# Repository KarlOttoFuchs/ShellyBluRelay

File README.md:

# ESP32C3 Relay Module

A BLE-enabled relay controller for home automation. Connect Shelly BLU sensors to switch 12-24V loads — no WiFi, no cloud, no app required.

> **Note:** This project is provided as-is. No support, issues, or pull requests will be addressed.

This repository also holds the **LED Strip Controller** (`FEHA-LSC-001`, in design): a 24 V COB
LED-strip dimmer in an inline printed tube. See [`Hardware/README.md`](Hardware/README.md) and
the design spec [`Docs/design/led-strip-controller-design.md`](Docs/design/led-strip-controller-design.md).
The rest of this README describes the relay module (`FEHA-RM-001` Rev A).

## Features

- **BTHome v2 sensor support** — Shelly BLU Button, Motion, and Door/Window sensors
- **30-second learning mode** — just press a button and trigger your sensor
- **Button-based timer presets** — 30s, 60s, 120s, or 300s (no computer needed)
- **Optional serial interface** — for advanced configuration and debugging
- **Safety-first design** — watchdog timer, fail-safe relay defaults (OFF on boot/reset)

## Default Settings

| Setting | Default | Description |
|---------|---------|-------------|
| Timer | 300 seconds | How long relay stays on after trigger |
| Retrigger | EXTEND | New triggers reset the timer countdown |
| State | UNCONFIGURED | Waiting for sensor registration |

## Quick Start (Button Only — No Serial Needed!)

1. **Power on** the module via USB-C or DC input → Status LED is OFF (unconfigured)
2. **Long press** the button for 2+ seconds → Status LED fast blinks (learning mode)
3. **Trigger your sensor** within 30 seconds (press button, wave at motion sensor, open door)
4. **Sensor registered** → Status LED slow blinks (listening, ready to use)
5. **Done!** Your sensor now controls the relay with a 5-minute timer

### Changing the Timer (Button Only)

While in listening mode (slow blink), use short presses to cycle through timer presets:

1. **Short press** (< 0.5 sec) → LED shows current preset with counted blinks
2. **Short press again** → Cycles to next preset
3. **Wait 5 seconds** → Preset saved automatically

| LED Blinks | Timer Duration |
|------------|----------------|
| 1 blink | 30 seconds |
| 2 blinks | 60 seconds |
| 3 blinks | 120 seconds |
| 4 blinks | 300 seconds (default) |

Settings persist across power cycles.

## LED Status Patterns

### Status LED (White)

| Pattern | Meaning |
|---------|---------|
| OFF | Unconfigured — no sensor registered |
| Fast blink (250ms) | Learning mode — 30 second window active |
| Slow blink (1s) | Listening — ready for sensor triggers |
| Solid ON | Relay active — timer running |

### Error LED (Red)

| Pattern | Meaning |
|---------|---------|
| 1 blink | Sensor battery low (< 20%) |
| 2 blinks | NVS storage error |
| 3 blinks | BLE initialization failure |

## Example: Motion-Activated Under-Counter Lights

Use a Shelly BLU Motion sensor to automatically turn on kitchen LED strip lighting.

**Wiring:**
- Connect 12V LED strip positive to relay **NO** (Normally Open) terminal
- Connect LED strip negative to power supply ground
- Connect relay **COM** (Common) to 12V power supply positive
- Power the module via the same 12V supply (DC input) or separate USB-C

**Setup:**
1. Power on the module
2. Long press button (2+ seconds) → fast blink
3. Walk past the motion sensor → sensor registered, slow blink
4. Short press button twice → cycles to 60-second preset (2 blinks)
5. Wait 5 seconds → preset saved

**Result:** Motion now triggers 60 seconds of under-counter lighting!

## Hardware Overview

- **MCU**: ESP32-C3-MINI-1 (RISC-V, BLE 5.0)
- **Relay**: 10A contacts (NO/NC/COM), 3VDC coil
- **Power**: USB-C (5V) or external DC (12-24V) with auto-switching
- **Interface**: Physical button + status/error LEDs

### GPIO Pinout

| GPIO | Function |
|------|----------|
| 0 | Error LED (red) |
| 7 | Relay control |
| 9 | User button (active low) |
| 10 | Status LED (white) |

## Serial Interface (Advanced)

Connect via USB at **115200 baud** for advanced configuration:

| Command | Description |
|---------|-------------|
| `STATUS` | Show current state, sensor info, timer settings |
| `RELAY ON` / `RELAY OFF` | Manual relay control for testing |
| `SET_TIMER <1-600>` | Set timer duration in seconds |
| `SET_RETRIGGER EXTEND` | New triggers reset timer (default) |
| `SET_RETRIGGER IGNORE` | Ignore triggers while relay active |
| `BLE_EVENTS` | Show last 10 sensor trigger events |
| `CLEAR_SENSOR` | Unregister sensor, return to unconfigured |
| `HELP` | List all commands |

## Building the Firmware

### Prerequisites

- ESP-IDF v5.1.x or v5.2.x LTS
- ESP32-C3 target configured

### Build & Flash

```bash
cd Firmware/esp32c3-relay-firmware

# First time only
idf.py set-target esp32c3

# Build and flash
idf.py build flash -p /dev/ttyUSB0

# Monitor serial output
idf.py monitor -p /dev/ttyUSB0
```

## Documentation

- [Architecture & Serial Protocol](Firmware/esp32c3-relay-firmware/docs/architecture.md)
- [Hardware Pin Mapping](Hardware/ESP32C3-Relay-Module-Rev-A/ESP32C3-Pin-Mapping.md)
- [Firmware README](Firmware/esp32c3-relay-firmware/README.md)

## License

MIT License — see [LICENSE](LICENSE) for details.

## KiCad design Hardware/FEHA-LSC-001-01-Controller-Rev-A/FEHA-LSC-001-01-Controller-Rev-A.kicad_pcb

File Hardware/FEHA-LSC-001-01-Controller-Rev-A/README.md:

# FEHA-LSC-001-01 Rev A — LED Strip Controller

24 V COB LED-strip controller, Shelly BLU / BLE triggered, ESP32-C3

**Status:** Manufacturing files generated 2026-10-07 — schematic and layout gates closed
2026-10-06 (50 × 30 mm, 4 layers, routed). Next: fab gate review (fiducials, position file). See [`DESIGN-CHANGES.md`](DESIGN-CHANGES.md) for the
change record and the design spec in
[`../../Docs/design/led-strip-controller-design.md`](../../Docs/design/led-strip-controller-design.md)
for intent, architecture and mechanical constraints — this README does not restate them.

## Project layout

- `FEHA-LSC-001-01-Controller-Rev-A.kicad_pro` / `.kicad_sch` / `.kicad_pcb`
- `Library/_FEHA-LSC-001.kicad_sym` + `Library/_FEHA-LSC-001.pretty/` — the **project-local** symbol and
  footprint libraries, wired in via `sym-lib-table` / `fp-lib-table` using `${KIPRJMOD}`. The
  nickname comes from the product part number, not the directory name.
- `Library/3DModels/` — STEP models, referenced as `${KIPRJMOD}/Library/3DModels/<name>.step`.
- `Library/_FEHA-LSC-001.kicad_blocks/` — the project **design-block** library (`design-block-lib-table`)
  for reusable schematic/layout fragments; empty until a block is saved into it from KiCad.
- `scripts/lcsc_to_kicad.py` — imports LCSC/EasyEDA parts into the project library.
- `scripts/setup_board.py` — board setup: outline and antenna notch, centre origin, keep-out
  rule areas, GND pours (re-runnable; see its docstring).
- `production/` — fab outputs from the KiCad Fabrication Toolkit (2026-10-07):
  `LED_Strip_Controller_A.zip` (Gerbers and drill files), `bom.csv`, `positions.csv`,
  `designators.csv`, `netlist.ipc`. The toolkit names the zip from the board title and
  revision, not the `FEHA-LSC-001-01-Controller-Rev-A-<fab>-<YYYYMMDD>.zip` convention.

## Tooling

`kicad-cli` is not on PATH:
`/Applications/KiCad/KiCad.app/Contents/MacOS/kicad-cli`

Files are **KiCad 10 format** (`version 20260306`).

## Revision history

- Rev A — initial design: schematic and layout complete, manufacturing files generated
  2026-10-07, not yet ordered.

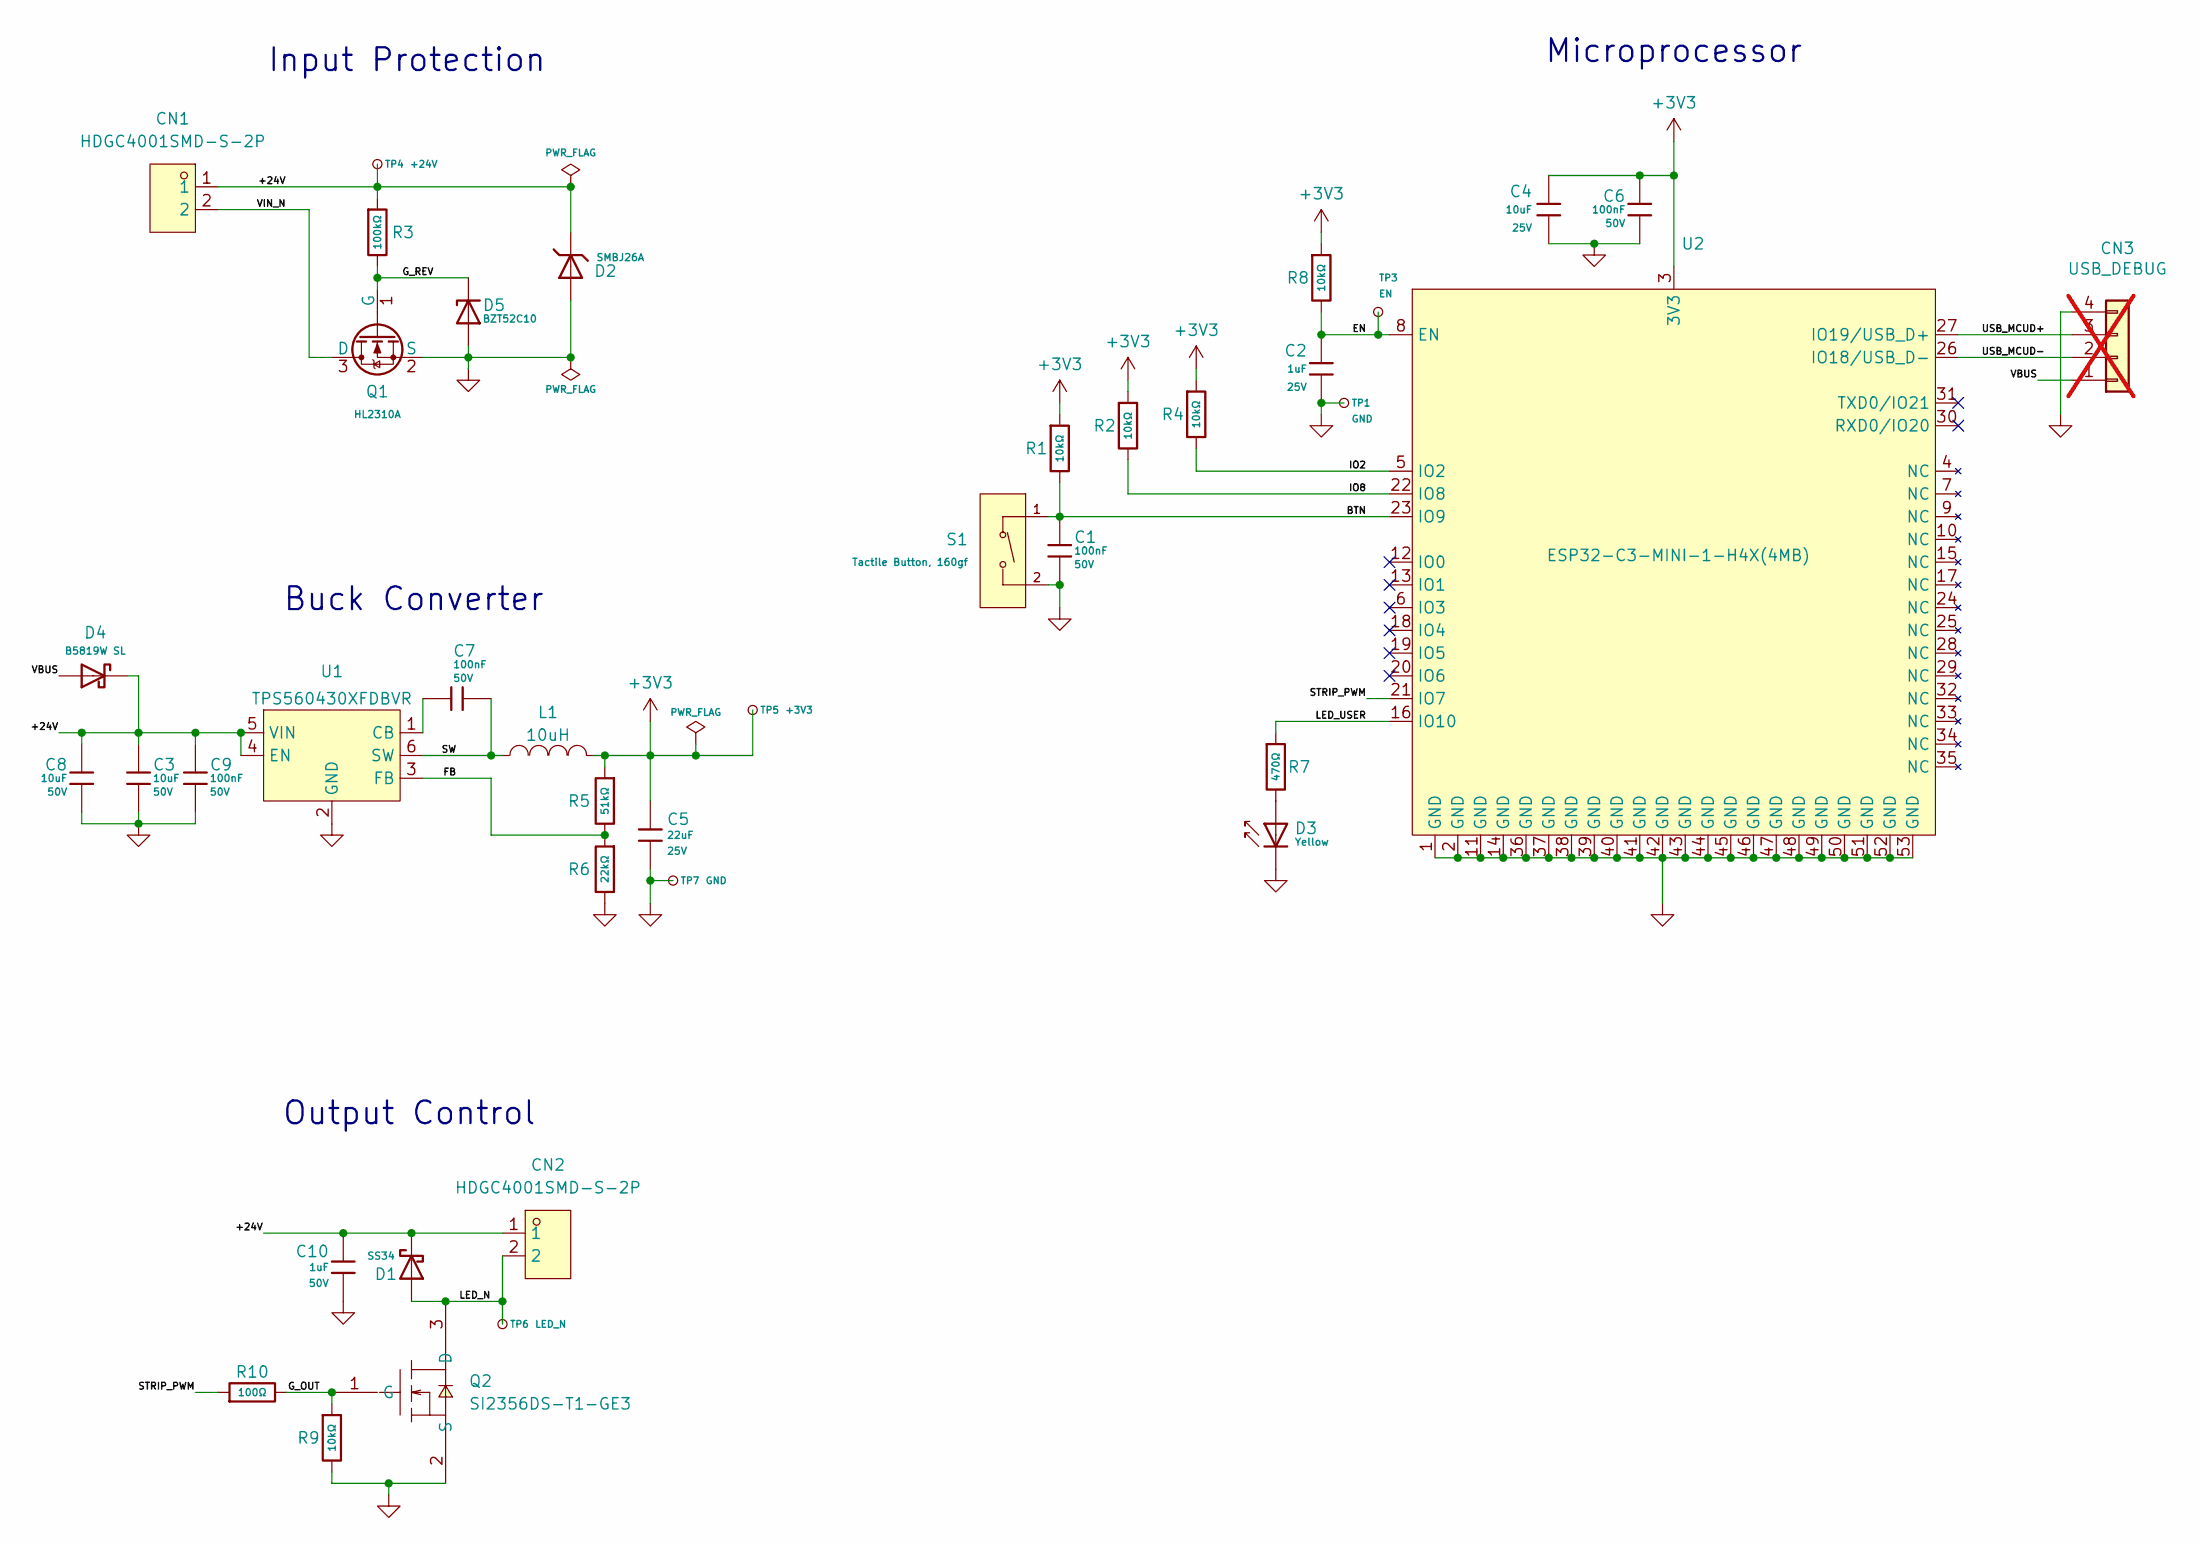
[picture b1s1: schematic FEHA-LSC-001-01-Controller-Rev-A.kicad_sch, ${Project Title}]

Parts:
C1, C6, C7, C9: 100nF; C_0402; Voltage Rated 50V; Tolerance ±10%; Part CL05B104KB54PNC; LCSC C307331
C2: 1uF; C_0402; Voltage Rated 25V; Tolerance ±10%; Part CL05A105KA5NQNC; LCSC C52923
C3, C8: 10uF; C_1206; Voltage Rated 50V; Tolerance ±10%; Part CL31A106KBHNNNE; LCSC C13585
C4: 10uF; C_0603; Voltage Rated 25V; Tolerance ±20%; Part CL10A106MA8NRNC; LCSC C96446
C5: 22uF; C_1206; Voltage Rated 25V; Tolerance ±10%; Part CL31A226KAHNNNE; LCSC C12891
C10: 1uF; C_0805; Voltage Rated 50V; Tolerance ±10%; Part CL21B105KBFNNNE; LCSC C28323
CN1, CN2: HDGC4001SMD-S-2P; CONN-SMD_2P-P4.00_HDGC4001SMD-S-2P; Mfr. Part # HDGC4001SMD-S-2P; LCSC Part # C5197184
CN3: USB_DEBUG; PinHeader_1x04_P2.54mm_Vertical_Lock; not fitted
D1: SS34; D_SMA; Forward Voltage (Vf@If) 550mV@3A; Reverse Voltage (Vr) 40V; Part SS34; LCSC C8678
D2: SMBJ26A; D_SMB; Part SMBJ26A; LCSC C19077580
D3: Yellow; D_0805; Part KT-0805Y; LCSC C2296
D4: B5819W SL; D_SOD-123; Forward Voltage (Vf@If) 600mV@1A; Reverse Voltage (Vr) 40V; Part B5819W SL; LCSC C8598
D5: BZT52C10; D_SOD-123; Part BZT52C10; LCSC C19077408
L1: 10uH; IND-SMD_L4.4-W4.2; Tolerance ±20%; Mfr. Part # FXL0420-100-M; LCSC Part # C177242
Q1: HL2310A; Q_SOT-23; Part HL2310A; LCSC C7420347
Q2: SI2356DS-T1-GE3; SOT-23_L2.9-W1.3-P1.90-LS2.4-BR; Mfr. Part # SI2356DS-T1-GE3; LCSC Part # C74127
R1, R2, R4, R8, R9: 10kΩ; R_0402; Overload Voltage (Max) 50V; Tolerance ±1%; Part 0402WGF1002TCE; LCSC C25744
R3: 100kΩ; R_0402; Overload Voltage (Max) 50V; Tolerance ±1%; Part 0402WGF1003TCE; LCSC C25741
R5: 51kΩ; R_0402; Overload Voltage (Max) 50V; Tolerance ±1%; Part 0402WGF5102TCE; LCSC C25794
R6: 22kΩ; R_0402; Overload Voltage (Max) 50V; Tolerance ±1%; Part 0402WGF2202TCE; LCSC C25768
R7: 470Ω; R_0402; Overload Voltage (Max) 50V; Tolerance ±1%; Part 0402WGF4700TCE; LCSC C25117
R10: 100Ω; R_0402; Overload Voltage (Max) 50V; Tolerance ±1%; Part 0402WGF1000TCE; LCSC C25076
S1: Tactile Button, 160gf; SW_TS-1088-AR02016; Voltage Rating (Dc) 12V; Part TS-1088-AR02016; LCSC C720477
TP1, TP7: GND; TestPoint_Pad_D1.5mm
TP3: EN; TestPoint_Pad_D1.5mm
TP4: +24V; TestPoint_Pad_D1.5mm
TP5: +3V3; TestPoint_Pad_D1.5mm
TP6: LED_N; TestPoint_Pad_D1.5mm
U1: TPS560430XFDBVR; SOT-23-6_L2.9-W1.6-P0.95-LS2.8-BR; Mfr. Part # TPS560430XFDBVR; LCSC Part # C523980
U2: ESP32-C3-MINI-1-H4X(4MB); WIFIM-SMD_ESP32-C3-MINI-1; Mfr. Part # ESP32-C3-MINI-1-H4X; LCSC Part # C41349510

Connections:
+3V3: C4.1, C5.1, C6.1, L1.1, R1.1, R2.1, R4.1, R5.1, R8.1, TP5.1 (1_1), U2.3 (3V3)
/+24V: C3.1, C8.1, C9.1, C10.1, CN1.1, CN2.1, D1.1, D2.1, D4.1, R3.1, TP4.1 (1_1), U1.4 (EN), U1.5 (VIN)
/BTN: C1.1, R1.2, S1.1 (A), U2.23 (IO9)
/EN: C2.1, R8.2, TP3.1 (1_1), U2.8 (EN)
/FB: R5.2, R6.1, U1.3 (FB)
/G_OUT: Q2.1 (G), R9.1, R10.2
/G_REV: D5.1, Q1.1 (G), R3.2
/IO2: R4.2, U2.5 (IO2)
/IO8: R2.2, U2.22 (IO8)
/LED_N: CN2.2, D1.2, Q2.3 (D), TP6.1 (1_1)
/LED_USER: R7.1, U2.16 (IO10)
/STRIP_PWM: R10.1, U2.21 (IO7)
/SW: C7.2, L1.2, U1.6 (SW)
/USB_MCUD+: CN3.3, U2.27 (IO19/USB_D+)
/USB_MCUD-: CN3.2, U2.26 (IO18/USB_D-)
/VBUS: CN3.1, D4.2
/VIN_N: CN1.2, Q1.3 (D)
GND: C1.2, C2.2, C3.2, C4.2, C5.2, C6.2, C8.2, C9.2, C10.2, CN3.4, D2.2, D3.1, D5.2, Q1.2 (S), Q2.2 (S), R6.2, R9.2, S1.2 (B), TP1.1 (1_1), TP7.1 (1_1), U1.2 (GND), U2.1 (GND), U2.2 (GND), U2.11 (GND), U2.14 (GND), U2.36 (GND), U2.37 (GND), U2.38 (GND), U2.39 (GND), U2.40 (GND), U2.41 (GND), U2.42 (GND), U2.43 (GND), U2.44 (GND), U2.45 (GND), U2.46 (GND), U2.47 (GND), U2.48 (GND), U2.49 (GND), U2.50 (GND), U2.51 (GND), U2.52 (GND), U2.53 (GND)
unnamed: D3.2, R7.2
unnamed: C7.1, U1.1 (CB)

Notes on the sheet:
Input Protection
Output Control
Microprocessor
Buck Converter

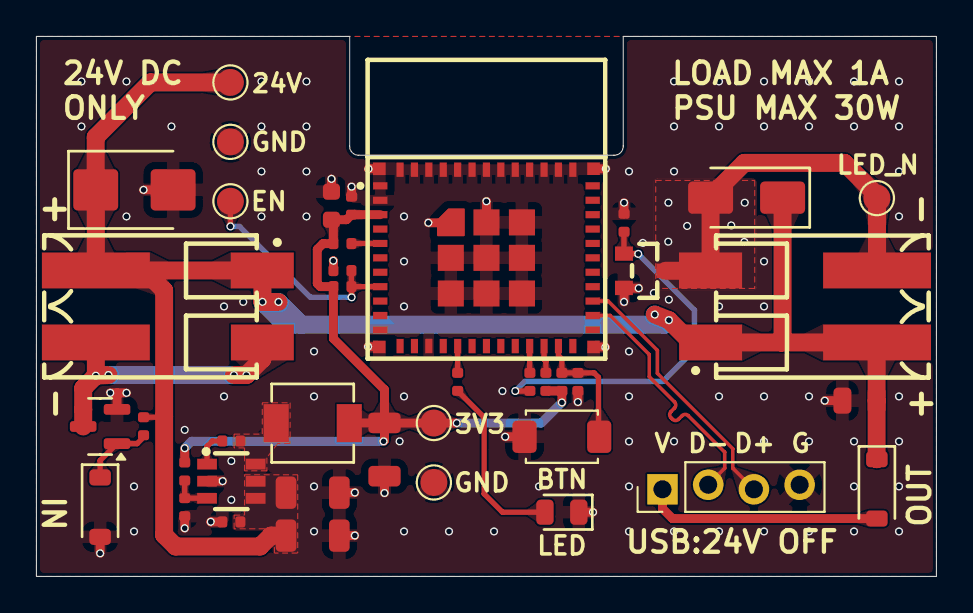
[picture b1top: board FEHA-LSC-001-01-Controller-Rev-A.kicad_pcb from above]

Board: 4 copper layers, 50.0 x 30.0 mm, 40 parts (0 on the bottom side), 20 nets.

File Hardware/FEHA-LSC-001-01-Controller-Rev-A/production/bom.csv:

Designator,Footprint,Quantity,Value,LCSC Part #
"C1, C6, C7, C9",C_0402,4,100nF,C307331
C10,C_0805,1,1uF,C28323
C2,C_0402,1,1uF,C52923
"C3, C8",C_1206,2,10uF,C13585
C4,C_0603,1,10uF,C96446
C5,C_1206,1,22uF,C12891
"CN1, CN2",CONN-SMD_2P-P4.00_HDGC4001SMD-S-2P,2,HDGC4001SMD-S-2P,C5197184
D1,D_SMA,1,SS34,C8678
D2,D_SMB,1,SMBJ26A,C19077580
D3,D_0805,1,Yellow,C2296
D4,D_SOD-123,1,B5819W SL,C8598
D5,D_SOD-123,1,BZT52C10,C19077408
L1,IND-SMD_L4.4-W4.2,1,10uH,C177242
Q1,Q_SOT-23,1,HL2310A,C7420347
Q2,SOT-23_L2.9-W1.3-P1.90-LS2.4-BR,1,SI2356DS-T1-GE3,C74127
"R1, R2, R4, R8, R9",R_0402,5,10kΩ,C25744
R10,R_0402,1,100Ω,C25076
R3,R_0402,1,100kΩ,C25741
R5,R_0402,1,51kΩ,C25794
R6,R_0402,1,22kΩ,C25768
R7,R_0402,1,470Ω,C25117
S1,SW_TS-1088-AR02016,1,"Tactile Button, 160gf",C720477
U1,SOT-23-6_L2.9-W1.6-P0.95-LS2.8-BR,1,TPS560430XFDBVR,C523980
U2,WIFIM-SMD_ESP32-C3-MINI-1,1,ESP32-C3-MINI-1-H4X(4MB),C41349510

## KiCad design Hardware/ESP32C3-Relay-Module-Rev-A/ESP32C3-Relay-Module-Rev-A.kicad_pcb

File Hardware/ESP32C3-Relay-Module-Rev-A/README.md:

# FEHA-RM-001 Rev A — ESP32-C3 Relay Module

BLE-triggered relay module: ESP32-C3-MINI-1-H4, SRD-03VDC-SL-C relay (3 V coil, AO3400A driver),
AP63203 3.3 V buck, USB-C or 5–24 V DC input, push button and status LEDs.

**Status:** Fabricated (JLCPCB). The KiCad files are frozen and must match the boards in hand.

## Project layout

- `ESP32C3-Relay-Module-Rev-A.kicad_pro` / `.kicad_sch` / `.kicad_pcb` — the design. The
  directory and file stem predate the `<PN>-<Slug>-Rev-<X>` convention and are kept as built.
- `ESP32C3-Pin-Mapping.md` — GPIO and connector map for this board.
- `production/` — the fabrication outputs that were ordered (`ESP32C3_Relay_Module_A.zip`, BOM,
  placement, IPC netlist).

## Libraries

This revision has **no project-local library**. Symbols and footprints resolve from machine-global
libraries: the custom library (`${CUSTOM_LIBRARY}`), the JLCPCB plugin library and KiCad's
3rd-party folder (`${KICAD8_3RD_PARTY}`). On a machine without them the schematic and board open
with missing parts.

## Revision history

- Rev A — first build.

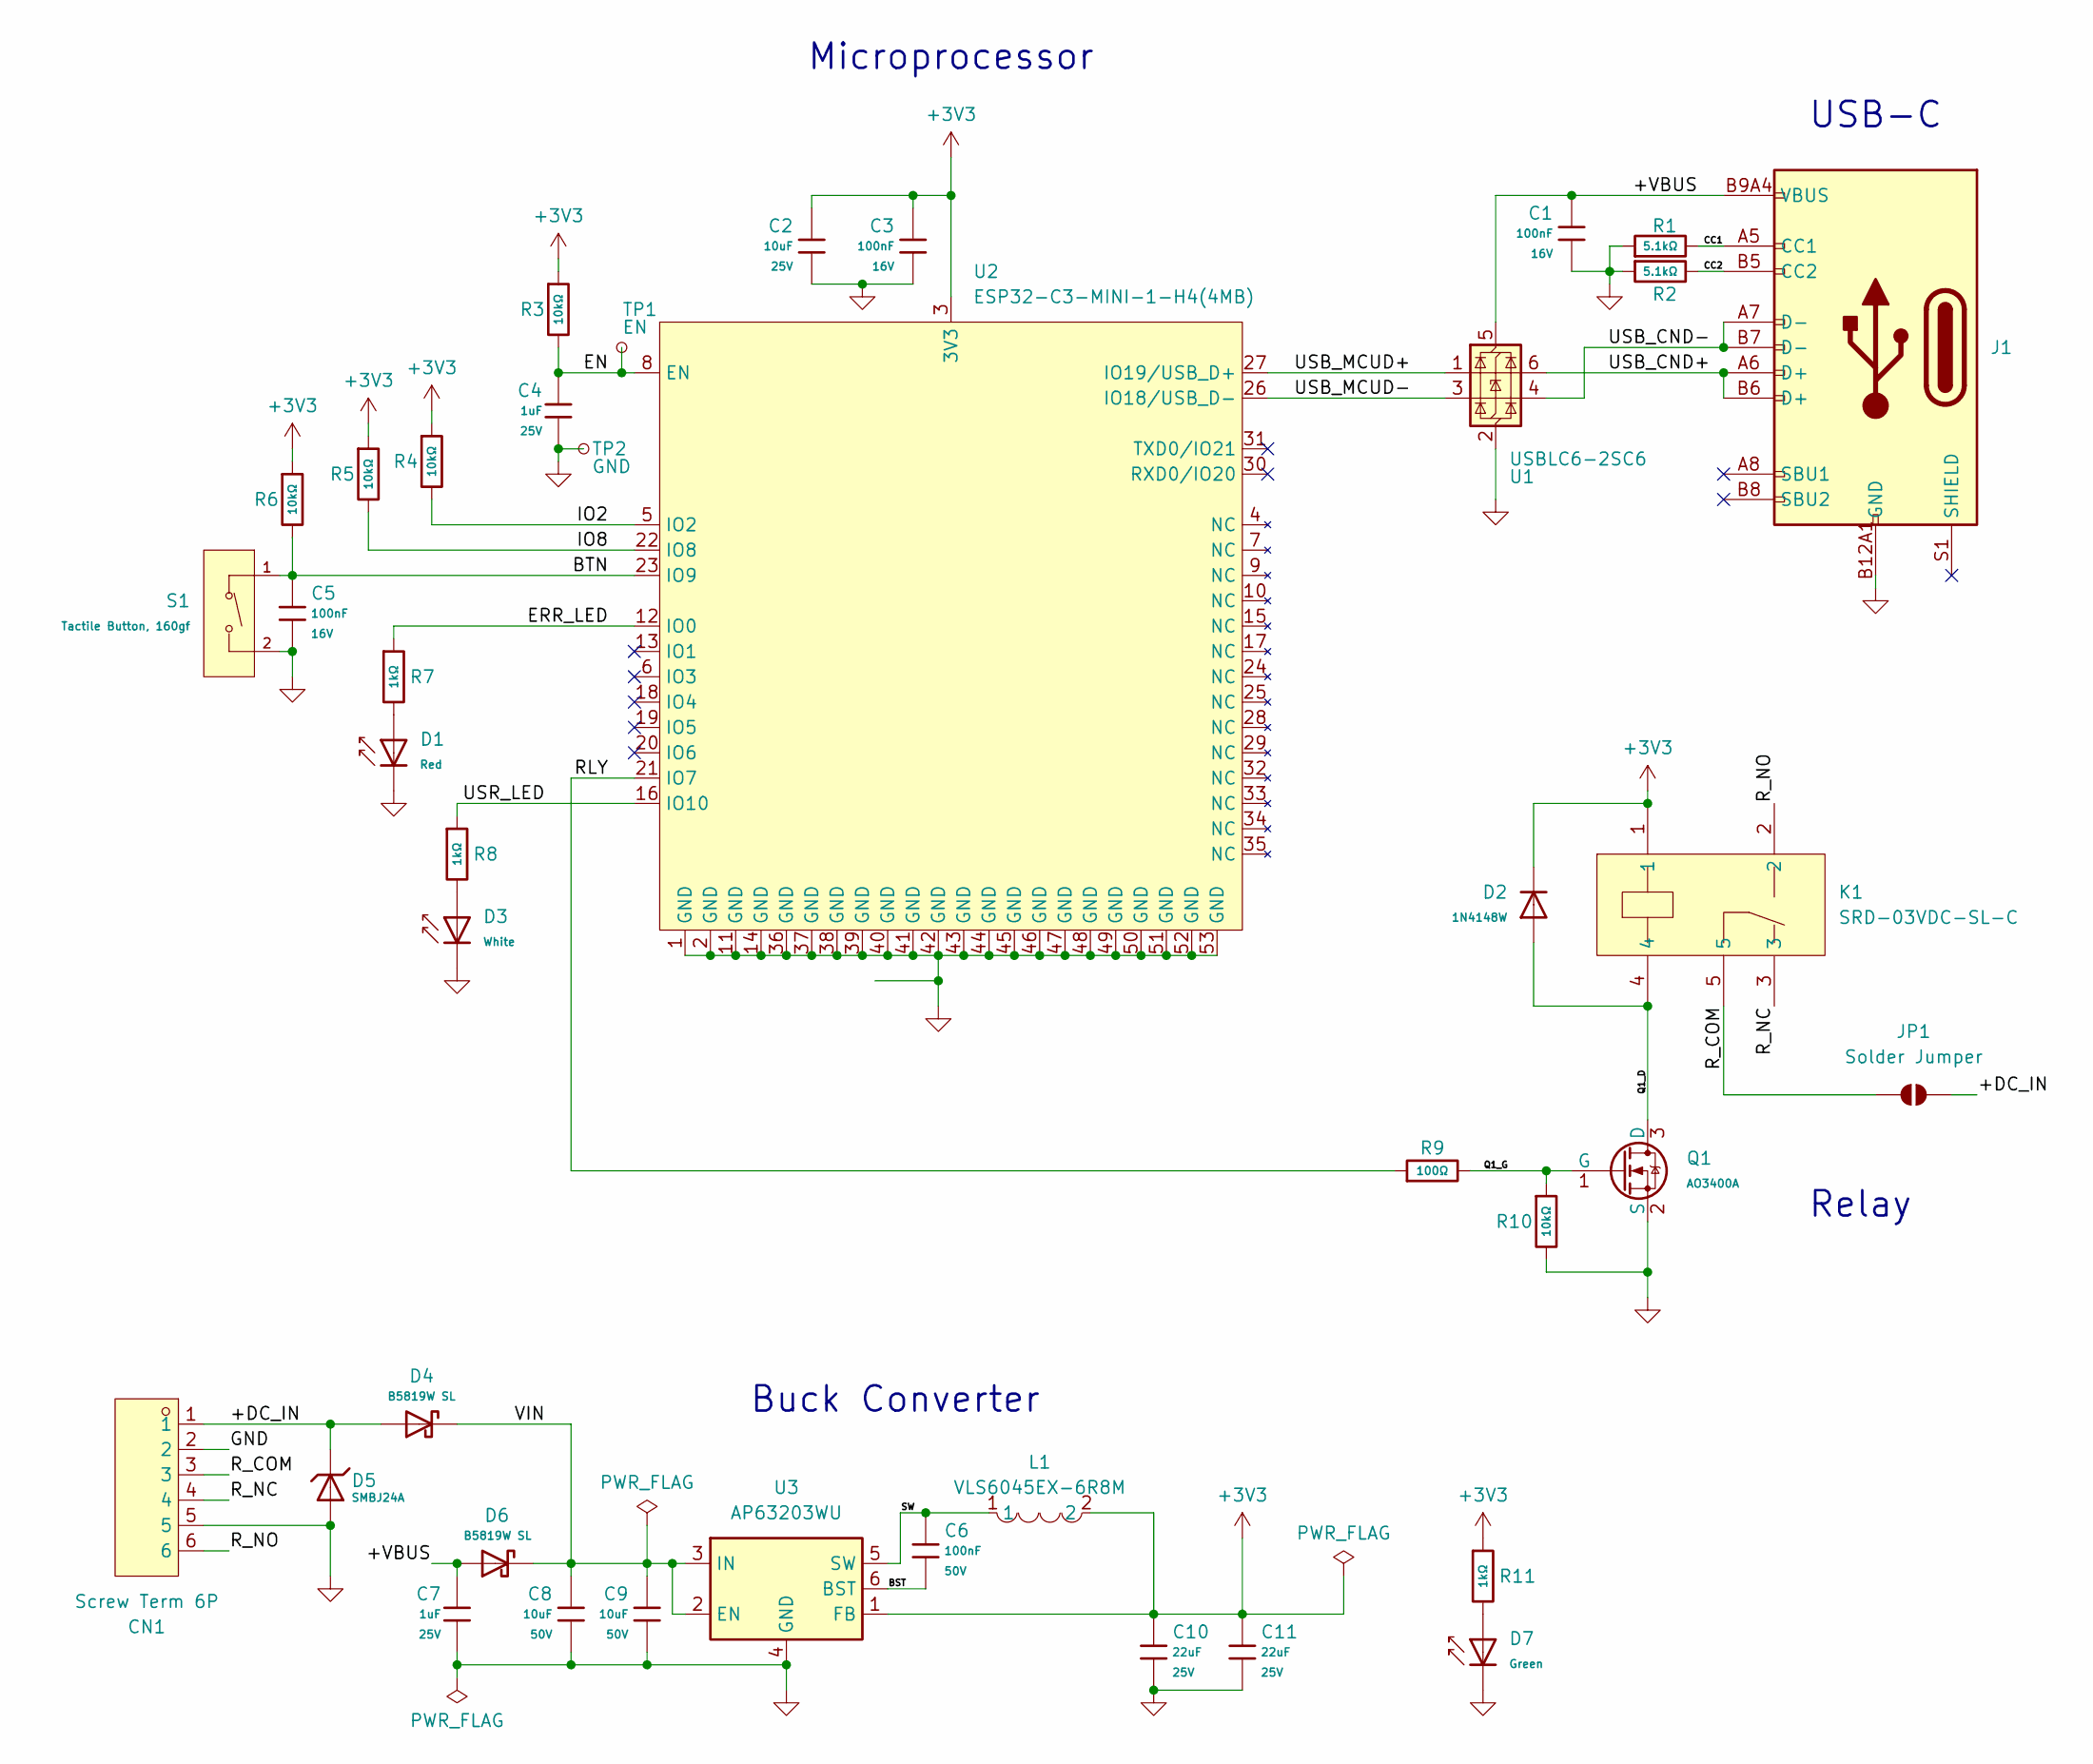
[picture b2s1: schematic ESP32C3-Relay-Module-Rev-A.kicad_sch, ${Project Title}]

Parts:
C1, C3, C5: 100nF; C_0402; Voltage Rated 16V; Tolerance ±10%; Part CL05B104KO5NNNC; LCSC C1525
C2: 10uF; C_0603; Voltage Rated 25V; Tolerance ±20%; Part CL10A106MA8NRNC; LCSC C96446
C4, C7: 1uF; C_0402; Voltage Rated 25V; Tolerance ±10%; Part CL05A105KA5NQNC; LCSC C52923
C6: 100nF; C_0603; Voltage Rated 50V; Tolerance ±10%; Part CC0603KRX7R9BB104; LCSC C14663
C8, C9: 10uF; C_1206; Voltage Rated 50V; Tolerance ±10%; Part CL31A106KBHNNNE; LCSC C13585
C10, C11: 22uF; C_1206; Voltage Rated 25V; Tolerance ±10%; Part CL31A226KAHNNNE; LCSC C12891
CN1: Screw Term 6P; CONN-TH_6P-MX128-5.08-GN01-06P-CU-Y-A; Mfr. Part # MX128-5.08-06P-GN01-Cu-Y-A; LCSC Part C5290379
D1: Red; D_0805; Forward Voltage (VF) 1.6V~2.6V; Part NCD0805R1; LCSC C84256
D2: 1N4148W; D_SOD-123; Forward Voltage (Vf@If) 1.25V@150mA; Reverse Voltage (Vr) 100V; Part 1N4148W; LCSC C7420318
D3: White; D_0805; Part KT-0805W; LCSC C34499
D4, D6: B5819W SL; D_SOD-123; Forward Voltage (Vf@If) 600mV@1A; Reverse Voltage (Vr) 40V; Part B5819W SL; LCSC C8598
D5: SMBJ24A; D_SMB; Part SMBJ24A; LCSC C19077578
D7: Green; D_0805; Part KT-0805G; LCSC C2297
J1: Connector, USB-TYPE-C-16P; TYPE-C-SMD_HX-TYPE-C-16PIN; Mfr. Part # USB-TYPE-C-019; LCSC C2927039
JP1: Solder Jumper; SolderJumper-2_P1.3mm_Open_RoundedPad1.0x1.5mm
K1: SRD-03VDC-SL-C; RELAY-TH_SRD-XXVDC-XL-C; Mfr. Part # SRD-03VDC-SL-C; LCSC Part # C24585
L1: VLS6045EX-6R8M; IND-SMD_L6.0-W6.0; Mfr. Part # VLS6045EX-6R8M; LCSC Part # C415364
Q1: AO3400A; Q_SOT-23; Part AO3400A; LCSC C20917
R1, R2: 5.1kΩ; R_0402; Overload Voltage (Max) 50V; Tolerance ±1%; Part 0402WGF5101TCE; LCSC C25905
R3, R4, R5, R6, R10: 10kΩ; R_0402; Overload Voltage (Max) 50V; Tolerance ±1%; Part 0402WGF1002TCE; LCSC C25744
R7, R8, R11: 1kΩ; R_0402; Overload Voltage (Max) 50V; Tolerance ±1%; Part 0402WGF1001TCE; LCSC C11702
R9: 100Ω; R_0402; Overload Voltage (Max) 50V; Tolerance ±1%; Part 0402WGF1000TCE; LCSC C25076
S1: Tactile Button, 160gf; SW_TS-1088-AR02016; Voltage Rating (Dc) 12V; Part TS-1088-AR02016; LCSC C720477
TP1: EN; TestPoint_Pad_D1.5mm
TP2: GND; TestPoint_Pad_D1.5mm
U1: USBLC6-2SC6; SOT-23-6; Mfr. Part # USBLC6-2SC6; LCSC Part # C7519
U2: ESP32-C3-MINI-1-H4(4MB); WIFIM-SMD_ESP32-C3-MINI-1; Mfr. Part # ESP32-C3-MINI-1-H4; LCSC Part # C2934569
U3: AP63203WU; TSOT-23-6; Mfr. Part # AP63203WU-7; LCSC Part # C780769

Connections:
+3V3: C2.1, C3.1, C10.1, C11.1, D2.1, K1.1, L1.2, R3.1, R4.1, R5.1, R6.1, R11.1, U2.3 (3V3), U3.1 (FB)
/+DC_IN: CN1.1, D4.2, D5.1, JP1.2 (B)
/+VBUS: C1.1, C7.1, D6.2, J1.A9B4 (VBUS), J1.B9A4 (VBUS), U1.5 (VBUS)
/BST: C6.2, U3.6 (BST)
/BTN: C5.1, R6.2, S1.1 (A), U2.23 (IO9)
/CC1: J1.A5 (CC1), R1.2
/CC2: J1.B5 (CC2), R2.2
/EN: C4.1, R3.2, TP1.1, U2.8 (EN)
/ERR_LED: R7.1, U2.12 (IO0)
/IO2: R4.2, U2.5 (IO2)
/IO8: R5.2, U2.22 (IO8)
/Q1_D: D2.2, K1.4, Q1.3 (D)
/Q1_G: Q1.1 (G), R9.2, R10.1
/RLY: R9.1, U2.21 (IO7)
/R_COM: CN1.3, JP1.1 (A), K1.5
/R_NC: CN1.4, K1.3
/R_NO: CN1.6, K1.2
/SW: C6.1, L1.1, U3.5 (SW)
/USB_CND+: J1.A6 (D+), J1.B6 (D+), U1.6 (I/O1)
/USB_CND-: J1.A7 (D-), J1.B7 (D-), U1.4 (I/O2)
/USB_MCUD+: U1.1 (I/O1), U2.27 (IO19/USB_D+)
/USB_MCUD-: U1.3 (I/O2), U2.26 (IO18/USB_D-)
/USR_LED: R8.1, U2.16 (IO10)
/VIN: C8.2, C9.2, D4.1, D6.1, U3.2 (EN), U3.3 (IN)
GND: C1.2, C2.2, C3.2, C4.2, C5.2, C7.2, C8.1, C9.1, C10.2, C11.2, CN1.2, CN1.5, D1.1, D3.1, D5.2, D7.1, J1.A12B1 (GND), J1.B12A1 (GND), Q1.2 (S), R1.1, R2.1, R10.2, S1.2 (B), TP2.1, U1.2 (GND), U2.1 (GND), U2.2 (GND), U2.11 (GND), U2.14 (GND), U2.36 (GND), U2.37 (GND), U2.38 (GND), U2.39 (GND), U2.40 (GND), U2.41 (GND), U2.42 (GND), U2.43 (GND), U2.44 (GND), U2.45 (GND), U2.46 (GND), U2.47 (GND), U2.48 (GND), U2.49 (GND), U2.50 (GND), U2.51 (GND), U2.52 (GND), U2.53 (GND), U3.4 (GND)
unnamed: D1.2, R7.2
unnamed: D3.2, R8.2
unnamed: D7.2, R11.2

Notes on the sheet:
Relay
Buck Converter
Microprocessor
USB-C

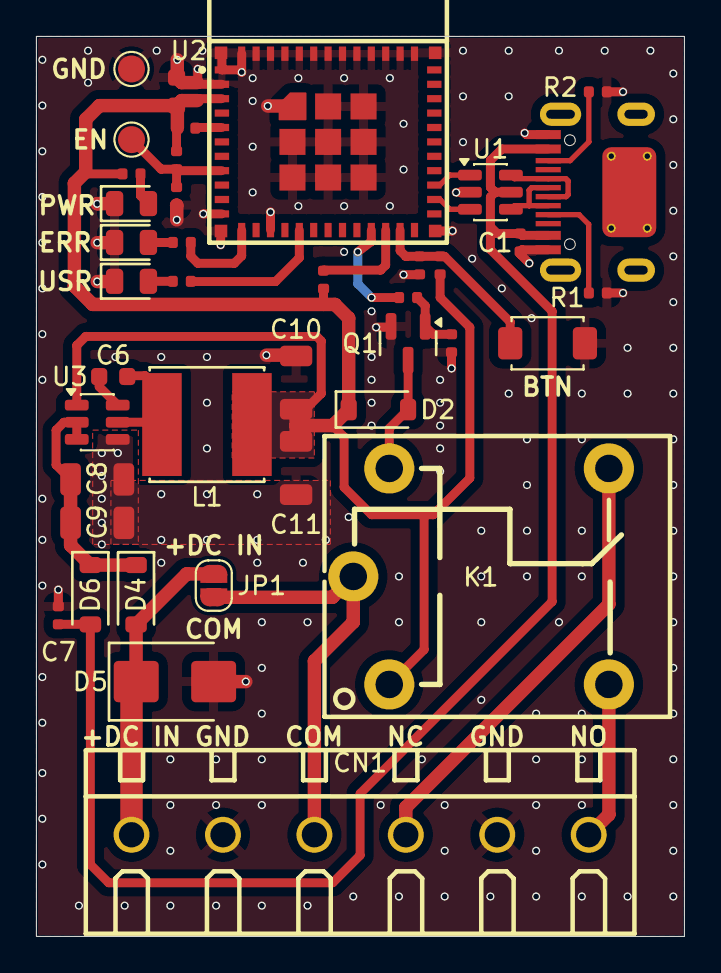
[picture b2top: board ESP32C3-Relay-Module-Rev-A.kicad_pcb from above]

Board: 2 copper layers, 36.0 x 50.0 mm, 41 parts (0 on the bottom side), 28 nets.

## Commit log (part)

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2026-01-21 Completed 1.1 & 1.2 and verified as working on hardware
